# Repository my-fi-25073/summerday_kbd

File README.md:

# summerday_kbd
Summerday ULP keyboard project

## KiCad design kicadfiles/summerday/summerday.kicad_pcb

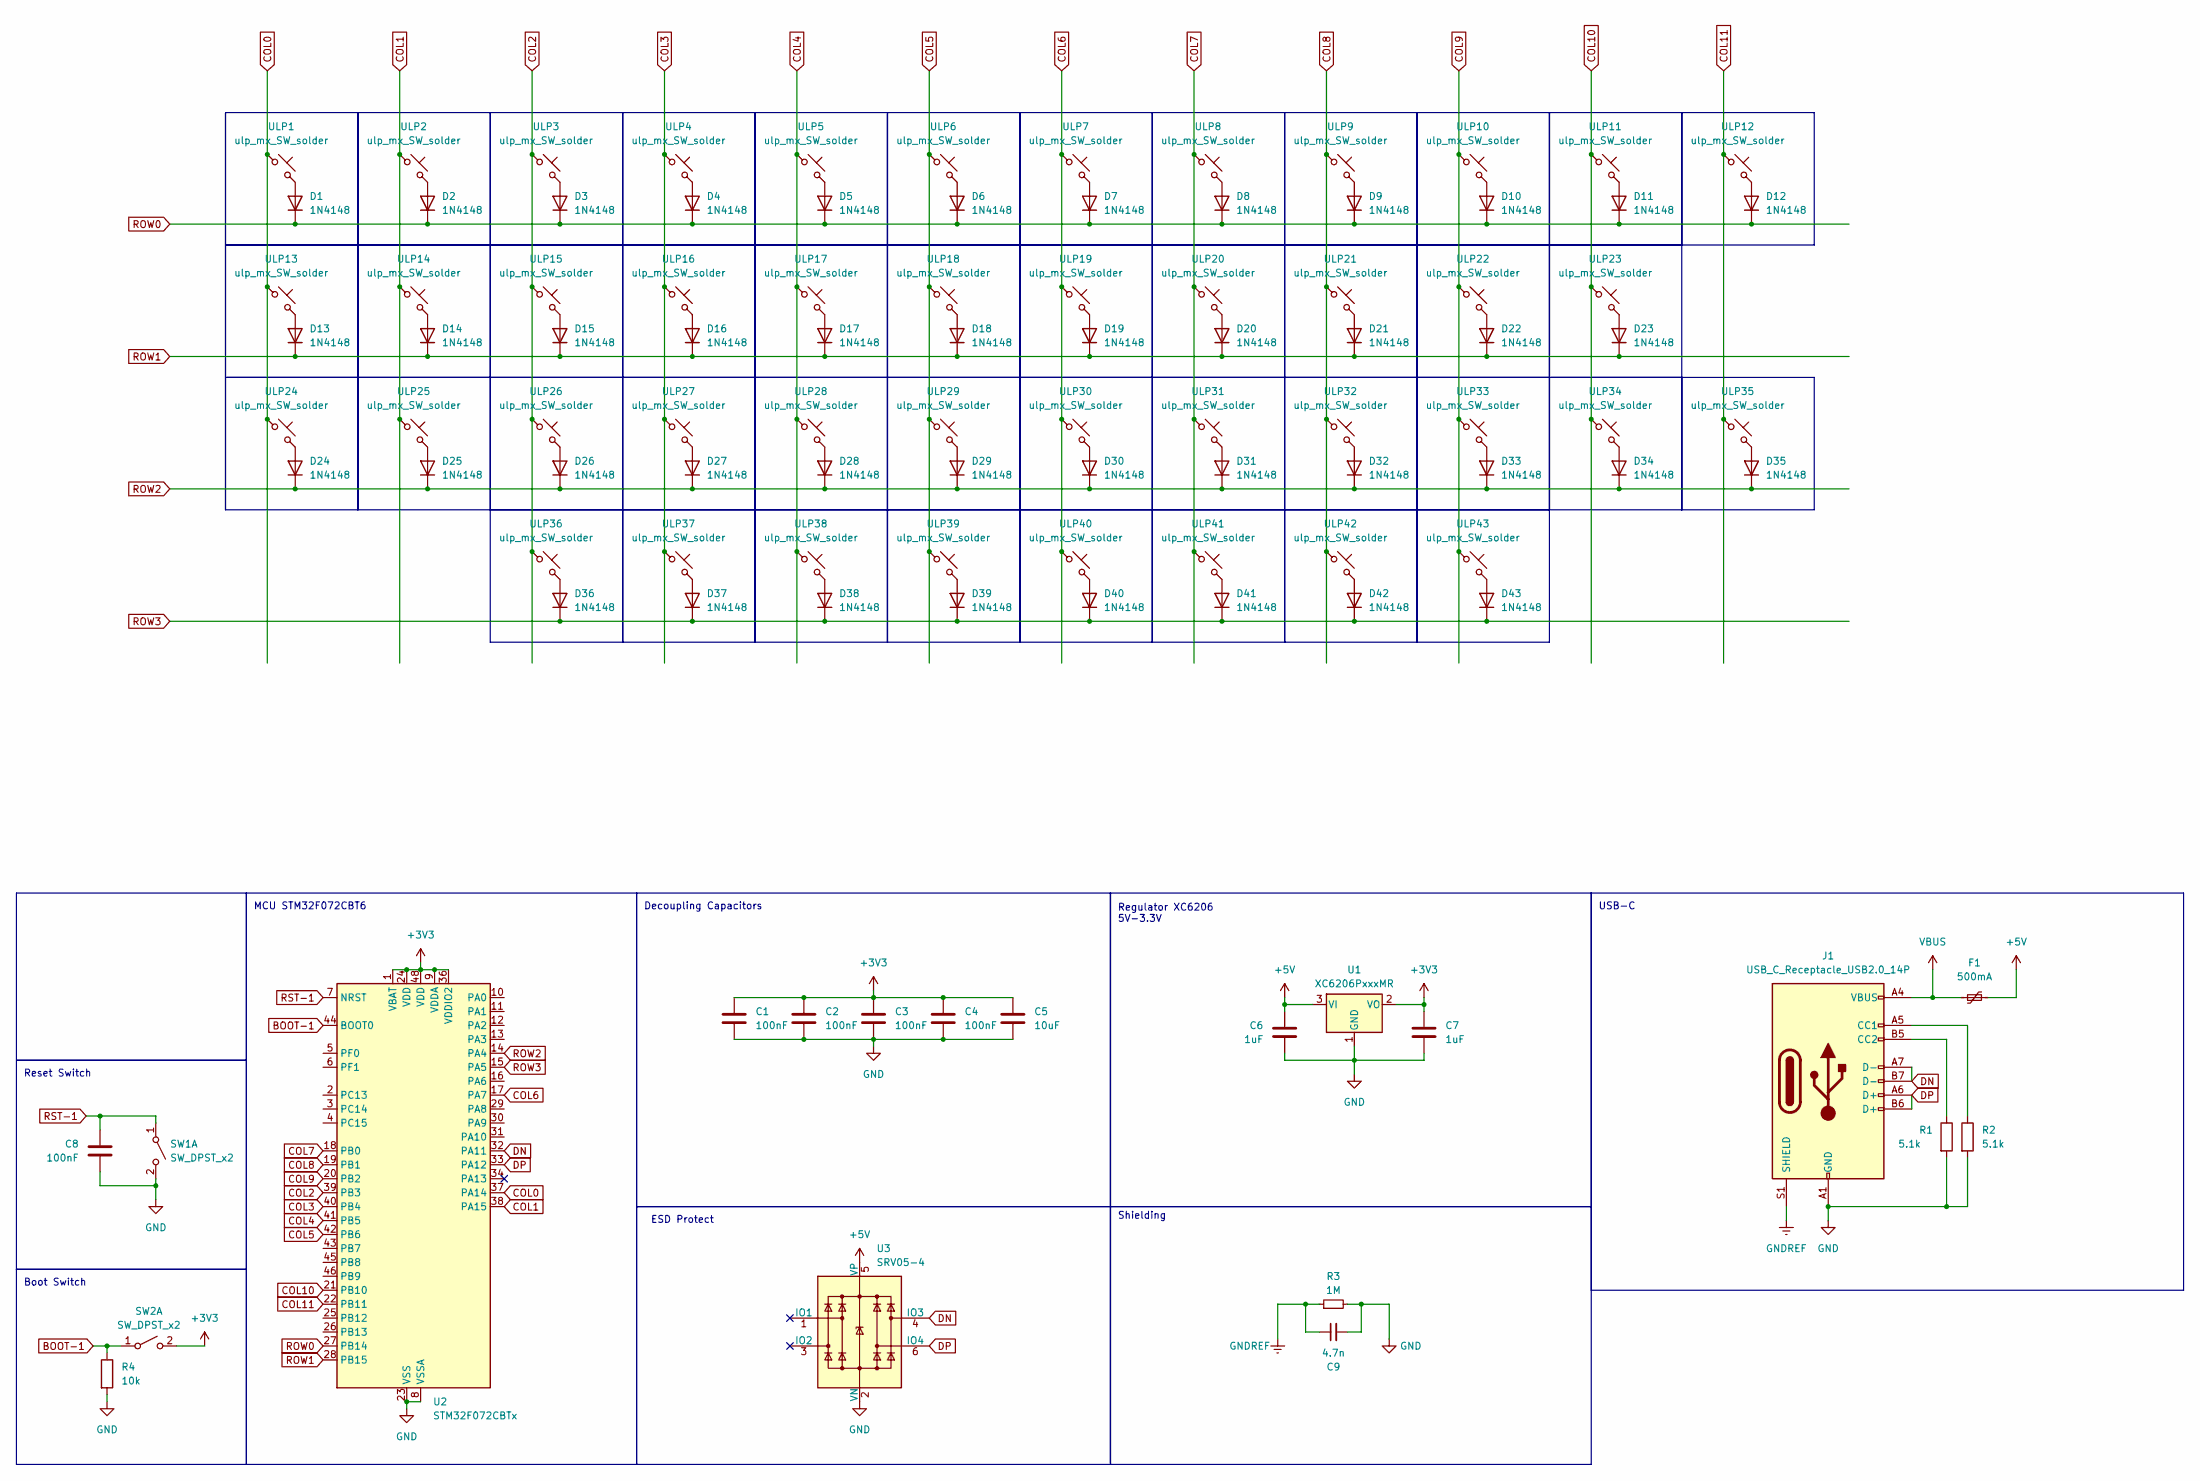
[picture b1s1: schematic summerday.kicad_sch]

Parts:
C1, C2, C3, C4, C8: 100nF; C_0402_1005Metric
C5: 10uF; C_0402_1005Metric
C6, C7: 1uF; C_0402_1005Metric
C9: 4.7n; C_0402_1005Metric
D1, D2, D3, D4, D5, D6, D7, D8, D9, D10, D11, D12, D13, D14, D15, D16, D17, D18, D19, D20, D21, D22, D23, D24, D25, D26, D27, D28, D29, D30, D31, D32, D33, D34, D35, D36, D37, D38, D39, D40, D41, D42, D43: 1N4148; D_SOD-323
F1: 500mA; Fuse_1206_3216Metric; LCSC C70076
J1: USB_C_Receptacle_USB2.0_14P; USB_C_Receptacle_HRO_TYPE-C-31-M-12; MPN C2894897
R1, R2: 5.1k; R_0402_1005Metric
R3: 1M; R_0402_1005Metric
R4: 10k; R_0402_1005Metric
SW1, SW2: SW_DPST_x2; SW_Push_1P1T_XKB_TS-1187A; MPN C318884
U1: XC6206PxxxMR; SOT-23-3; MPN C5148692
U2: STM32F072CBTx; LQFP-48_7x7mm_P0.5mm; MPN C81720
U3: SRV05-4; SOT-23-6; MPN C7420376
ULP1, ULP2, ULP3, ULP4, ULP5, ULP6, ULP7, ULP8, ULP9, ULP10, ULP11, ULP12, ULP13, ULP14, ULP15, ULP16, ULP17, ULP18, ULP19, ULP20, ULP21, ULP22, ULP23, ULP24, ULP25, ULP26, ULP27, ULP28, ULP29, ULP30, ULP31, ULP32, ULP33, ULP34, ULP35, ULP36, ULP37, ULP38, ULP39, ULP40, ULP41, ULP42, ULP43: ulp_mx_SW_solder; SW_MX_ULP_1u_Plate

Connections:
+3V3: C1.1, C2.1, C3.1, C4.1, C5.1, C7.1, SW2.2 (B), U1.2 (VO), U2.1 (VBAT), U2.9 (VDDA), U2.24 (VDD), U2.36 (VDDIO2), U2.48 (VDD)
+5V: C6.1, F1.2, U1.3 (VI), U3.5 (VP)
BOOT-1: R4.1, SW2.1 (A), U2.44 (BOOT0)
COL0: U2.37 (PA14), ULP1.1, ULP13.1, ULP24.1
COL1: U2.38 (PA15), ULP2.1, ULP14.1, ULP25.1
COL2: U2.39 (PB3), ULP3.1, ULP15.1, ULP26.1, ULP36.1
COL3: U2.40 (PB4), ULP4.1, ULP16.1, ULP27.1, ULP37.1
COL4: U2.41 (PB5), ULP5.1, ULP17.1, ULP28.1, ULP38.1
COL5: U2.42 (PB6), ULP6.1, ULP18.1, ULP29.1, ULP39.1
COL6: U2.17 (PA7), ULP7.1, ULP19.1, ULP30.1, ULP40.1
COL7: U2.18 (PB0), ULP8.1, ULP20.1, ULP31.1, ULP41.1
COL8: U2.19 (PB1), ULP9.1, ULP21.1, ULP32.1, ULP42.1
COL9: U2.20 (PB2), ULP10.1, ULP22.1, ULP33.1, ULP43.1
COL10: U2.21 (PB10), ULP11.1, ULP23.1, ULP34.1
COL11: U2.22 (PB11), ULP12.1, ULP35.1
DN: J1.A7 (D-), J1.B7 (D-), U2.32 (PA11), U3.4 (IO3)
DP: J1.A6 (D+), J1.B6 (D+), U2.33 (PA12), U3.6 (IO4)
GND: C1.2, C2.2, C3.2, C4.2, C5.2, C6.2, C7.2, C8.2, C9.2, J1.A1 (GND), J1.A12 (GND), J1.B1 (GND), J1.B12 (GND), R1.2, R2.2, R3.2, R4.2, SW1.2 (B), U1.1 (GND), U2.8 (VSSA), U2.23 (VSS), U2.35 (VSS), U2.47 (VSS), U3.2 (VN)
GNDREF: C9.1, J1.S1 (SHIELD), R3.1
unnamed: D1.2 (A), ULP1.2
unnamed: D2.2 (A), ULP2.2
unnamed: D3.2 (A), ULP3.2
unnamed: D4.2 (A), ULP4.2
unnamed: D5.2 (A), ULP5.2
unnamed: D6.2 (A), ULP6.2
unnamed: D7.2 (A), ULP7.2
unnamed: D8.2 (A), ULP8.2
unnamed: D9.2 (A), ULP9.2
unnamed: D10.2 (A), ULP10.2
unnamed: D11.2 (A), ULP11.2
unnamed: D12.2 (A), ULP12.2
unnamed: D13.2 (A), ULP13.2
unnamed: D14.2 (A), ULP14.2
unnamed: D15.2 (A), ULP15.2
unnamed: D16.2 (A), ULP16.2
unnamed: D17.2 (A), ULP17.2
unnamed: D18.2 (A), ULP18.2
unnamed: D19.2 (A), ULP19.2
unnamed: D20.2 (A), ULP20.2
unnamed: D21.2 (A), ULP21.2
unnamed: D22.2 (A), ULP22.2
unnamed: D23.2 (A), ULP23.2
unnamed: D24.2 (A), ULP24.2
unnamed: D25.2 (A), ULP25.2
unnamed: D26.2 (A), ULP26.2
unnamed: D27.2 (A), ULP27.2
unnamed: D28.2 (A), ULP28.2
unnamed: D29.2 (A), ULP29.2
unnamed: D30.2 (A), ULP30.2
unnamed: D31.2 (A), ULP31.2
unnamed: D32.2 (A), ULP32.2
unnamed: D33.2 (A), ULP33.2
unnamed: D34.2 (A), ULP34.2
unnamed: D35.2 (A), ULP35.2
unnamed: D36.2 (A), ULP36.2
unnamed: D37.2 (A), ULP37.2
unnamed: D38.2 (A), ULP38.2
unnamed: D39.2 (A), ULP39.2
unnamed: D40.2 (A), ULP40.2
unnamed: D41.2 (A), ULP41.2
unnamed: D42.2 (A), ULP42.2
unnamed: D43.2 (A), ULP43.2
unnamed: J1.A5 (CC1), R2.1
unnamed: J1.B5 (CC2), R1.1
ROW0: D1.1 (K), D2.1 (K), D3.1 (K), D4.1 (K), D5.1 (K), D6.1 (K), D7.1 (K), D8.1 (K), D9.1 (K), D10.1 (K), D11.1 (K), D12.1 (K), U2.27 (PB14)
ROW1: D13.1 (K), D14.1 (K), D15.1 (K), D16.1 (K), D17.1 (K), D18.1 (K), D19.1 (K), D20.1 (K), D21.1 (K), D22.1 (K), D23.1 (K), U2.28 (PB15)
ROW2: D24.1 (K), D25.1 (K), D26.1 (K), D27.1 (K), D28.1 (K), D29.1 (K), D30.1 (K), D31.1 (K), D32.1 (K), D33.1 (K), D34.1 (K), D35.1 (K), U2.14 (PA4)
ROW3: D36.1 (K), D37.1 (K), D38.1 (K), D39.1 (K), D40.1 (K), D41.1 (K), D42.1 (K), D43.1 (K), U2.15 (PA5)
RST-1: C8.1, SW1.1 (A), U2.7 (NRST)
VBUS: F1.1, J1.A4 (VBUS), J1.A9 (VBUS), J1.B4 (VBUS), J1.B9 (VBUS)

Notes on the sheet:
USB-C
Reset Switch
Decoupling Capacitors
Regulator XC6206 5V-3.3V
Shielding
ESD Protect
Boot Switch
MCU STM32F072CBT6

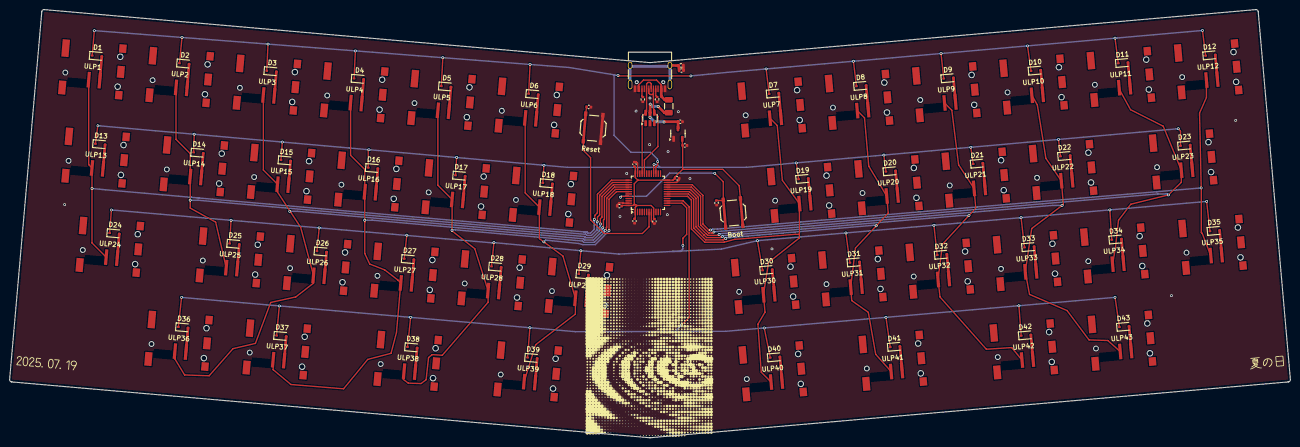
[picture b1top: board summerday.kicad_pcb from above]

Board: 2 copper layers, 278.4 x 93.1 mm, 106 parts (0 on the bottom side), 70 nets.

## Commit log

2025-07-23 Added stm32 based sch, pcb
2025-07-28 updated pcb artworks
2025-08-02 Almost Finished pcb artworks
